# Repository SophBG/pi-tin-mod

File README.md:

# Pi Tin mod

Personal build of jackw01's [Pi Tin](https://github.com/jackw01/pi-tin) (3D-printed clamshell version, KiCad 10). It adds 10 RGB LEDs under the buttons, a centred speaker, a USB-drive mode for the ROMs, and ESD protection on USB, and runs on an Orange Pi Zero 2W. The upstream [build guides](https://jackw01.github.io/pi-tin/) still apply. License: CERN-OHL-W v2.

## Boards

| | Main | Display |
|---|---|---|
| Size | 89.15 × 55.65 mm | 39.15 × 46.15 mm |
| **Thickness** | **1.0 mm** | **0.6 mm** |
| Layers, copper | 2, 1 oz | 2, 1 oz |
| Min. track / hole / via | 0.2 / 0.3 / 0.6 mm | 0.2 / 0.3 / 0.6 mm |

Gerbers for both boards are in `fab/`.

## Main board changes

| Function | Parts | Notes |
|---|---|---|
| RGB LEDs | D1–D10 (WS2812B-2020) | Chain: D1 → D10. D1–D4 ABXY, D5 Start, D6 Select, D7–D10 D-pad. |
| LED driver | U106 74AHCT1G125, R130 330 Ω | Input: SPI MOSI. Enabled only by the second SPI chip select on header pin 21, so the display (first chip select) never reaches the LEDs. |
| | R131 10 k, R132 100 k | R131: buffer off at boot. R132: data line low. |
| USB detect | R133/R134 100 k | VBUS divider to header pin 8 |
| USB-drive mode | U107 USBLC6-2SC6, TP132 (D+), TP133 (D−) | Wire TP132/TP133 by hand to the Orange Pi's USB D+/D− (see Hardware notes). Optional. |
| Backlight PWM | Header pins 16 and 18 swapped | Backlight on pin 16, UP on pin 18 (upstream: the other way round). Pin 16 is a hardware PWM on the Orange Pi. |

**Footprints for both suppliers:**
- **J101:** HCTL HC-TYPE-C-16P-01A or GCT USB4105-GF-A.
- **8-pin FPC:** XYECONN FPC09-Q1.0-8AH2.0 or Molex 200528-0080.
- **50-pin FPC:** JUSHUO AFC07-S50ECA-00 or Amphenol F32Q-1A7H1-11050.

**Not fitted:** C107, C110, C111, D103, FB103, FB104, R103, R109, R118, R125 (main board); J101 (display board).

**LEDs from LCSC:** XINGLIGHT XL-2020RGBC-WS2812B. Check its pin-1 mark before soldering.

## Display

2.8" ILI9341, 240 × 320, 50-pin 0.5 mm FPC, with 4-wire resistive touch. The touch is not used, but it gives the 4.0 mm thickness the case expects and protects the screen.

- **Known good:** Adafruit 1774 (MI0283QT-11), or BuyDisplay ER-TFT028-4 with the "Resistive Touch" option.
- **Outline:** 50.2 × 69.3 × 4.0 mm. Active area: 43.2 × 57.6 mm.
- **FPC:** leaves the middle of a short side, about 25.5 mm wide and 27 mm long. It must have plug-in contacts: 37-pin solder-tail panels don't fit.
- **Pinout:** 1 LEDK · 2–5 LEDA · 6–9 IM0–3 · 10 RESET · 33 SDO · 34 SDI · 35 RD · 36 WRX = D/C · 37 DCX = SCK · 38 CS · 40–42 VCC · 43 GND. Pins 44–47 (touch) only go to test points.
- **Without touch** (2.8 mm thick):
  - **Spacer:** add a 1.2 mm frame between the bezel and the panel, 50.2 × 69.3 mm outside with a 60 × 45.5 mm window (the size of the bezel opening).
  - **Screen protector:** 61–62 × 46–47 mm, for example a protector for the bottom screen of an original 3DS. Subtract its thickness from the frame.

## Speaker

| Space | |
|---|---|
| Outline | 15 × 11 mm |
| Height | 3.4 mm, from the PCB to the faceplate ledge |
| Pads (LS101) | 2.5 × 1.7 mm, centres 9.85 mm apart across the width, about 1 mm from the short end away from the D-pad |

- **Spring contacts (no soldering):** Same Sky CMS-151125-078S-67 (8 Ω) or CMS-151125-076S-67 (6 Ω), 15 × 11 × 2.5 mm. Contacts face the PCB.
- **Wired (soldered):**
  - **Size:** 15 × 11 mm, body at most 3.3 mm tall, 6–8 Ω, 0.5 W or more.
  - **Wiring:** cut the leads to about 1 cm and solder them to the LS101 pads. Polarity does not matter.
  - **Lead routing:** the pocket wall stops 1 mm above the PCB, so the leads pass under it.
- **Taller spring speakers** (for example the 1511 ones with a 3.0–3.3 mm body):
  - **Faceplate:** lower the pocket ledge to the body height plus about 0.4 mm.
  - **Contacts:** the springs must land on the pads.
- **H106 clearance:** the speaker body starts about 0.4 mm past the edge of the H106 mounting hole. Check that the screw head doesn't press on it.

## Other parts

- **Interconnect cable:** 8-pin FFC, 1.0 mm pitch, contacts on the same side.
  - **Length:** **50 mm**. The shortest path through the hinge is about 35–38 mm, and the cable must not be under tension.
  - **Parts:** GCT 10-08-A-0050-C-4-08-4-T or JUSHUO JS10A-08P-050-4-8.
- **Battery:** 1-cell LiPo, about 2000 mAh, 8 × 38 × 60 mm, with protection circuit and a JST PH 2-pin plug, for example PKCell LP803860. The pocket is about 66.8 × 38.8 × 8 mm.
  - **Polarity:** J102 pin 1 is BAT+ (it goes to F101). Check that the red wire lands on it before plugging in.
- **Shoulder buttons:** E-Switch TL3336AF160Q.
- **Wi-Fi antenna:** 2.4/5 GHz flex (FPC) antenna with an **MHF4 (IPEX-4)** plug and 0.81 mm cable, flat part at most about 27 × 12 mm. The one that comes with the board fits the connector; use it if it is small enough. U.FL (MHF1) antennas don't fit this connector.

## 3D printing

- **Faceplate:** `3d/faceplate/faceplate_v3_with_led_pockets.stl`. It is `v3.stl` with the LED pockets and collars merged, plus:
  - **Thicker skin:** most 0.8 mm panels are now 1.7 mm (`faceplate_thickening.stl`). That leaves 1.9 mm above the main board and 2.9 mm above the Orange Pi. The USB-C sits on the back, but its four shell legs come through: trim them flush on the front if they stick out more than 1.5 mm. Left as they were: the button rings, the LED pockets and light tunnels (with 0.5 mm around them), the Start/Select and side buttons, and the speaker.
  - **Over the Orange Pi:** its parts were placed from Orange Pi's DXF of the board; they are in the same places as on the Pi Zero. The panels over the HDMI and the Wi-Fi module stay 0.8 mm. The pocket over the two USB-C leaves 3.4 mm (the connectors are about 3.2 mm).
  - **ABXY LED pockets:** the collars left small gaps beside the cutter (and the one at the bottom right was open on one side); `faceplate_pocket_fill.stl` fills them, so each pocket is exactly the cutter's shape, like the D-pad ones.
  - **Button key tabs:** the light tunnels end where the B (left and right) and Y (bottom) tabs are and had taken their lower 0.8 mm; the tabs are whole again. Light still passes beside and under them.
  - **microSD closure:** 1.7 mm instead of 0.8 mm, leaving 2.9 mm above the Orange Pi for the card and its slot.
  - **To rebuild it:** open `faceplate_led_cuts.scad` with the five STLs in the same folder.
  - **In Blender:** Union with the collars, the pocket fill and the thickening first, then Difference with the cutter, then Union with the key tabs (in the `.scad`), all with the Exact solver.
- **Lower case:** `3d/case/p101_lower_case_fixed.STL`.
- **Display housing, bezel, buttons:** the upstream STL files.

## Orange Pi Zero 2W

`software/orange_pi/` sets everything up on Armbian (Debian, "current" kernel). The sound and backlight drivers are Armbian kernel patches, so mainline kernels won't work. Do the Armbian first-boot setup over SSH, then:

```
cd software/orange_pi
sudo ./install.sh            # ROM_SIZE=16G sudo ./install.sh for a bigger ROM drive
sudo reboot
sudo ./check.sh --test       # status, then backlight, LEDs, sound and buttons
```

What it sets up:
- **Overlay `pitin-opi-zero2w.dts`:**
  - display: `mi0283qt` driver on SPI1 CS0 at 50 MHz, `rotation = <90>` (use 270 if the picture is upside down);
  - backlight: PWM4 at 20 kHz, as `/sys/class/backlight/pitin-backlight`;
  - LEDs: spidev on CS1, with PH8 as the chip select;
  - sound: I2S0 to the MAX98357A, through the Armbian kernel's AHUB driver;
  - the 15 buttons as one gamepad;
  - power button: systemd powers off;
  - power-off line on pin 5;
  - USB cable detect;
  - UART0 off.
- **RetroArch** starts on the screen at boot. There is no EmulationStation.
  - **Save states:** the game state is saved and restored automatically, including at power-off.
  - **Cores:** they come from the Debian packages. If the packaged RetroArch lacks KMS, `install.sh` builds it from source.
- **ROM drive:** a FAT32 image (`~/roms.img`) mounted on `~/roms`, with a folder per console. Plugged into a computer, it shows up there as a USB drive (`pitin-usbd`); a charger changes nothing.
- **Sound:** both channels are mixed for the single amplifier. Set the volume with `amixer sset Master 60%`.
- **`pitin-daemon`:** screen brightness, volume, the LEDs and a settings page (`pitin-web.html`). Settings are kept across reboots.
  - **LED effects:** each LED has its own colour. Off, static (steady), wave (a rainbow, or the LEDs' own colours, travels from LED to LED in a chosen order), fade (all LEDs change colour together) and reactive (a pressed button lights the LEDs beside it: two for the D-pad and ABXY, its own side for the shoulders).
  - **Settings page:** LEDs, uploading ROMs over Wi-Fi (sorted into the console folders by file type) and deleting them, screen brightness, volume, status, the console's name on the network (Console tab, "Change"), restart and power off. Works on a phone or a computer, in French or English depending on the browser's language.
  - **Address:** `http://<name>.local` on most phones and computers (`avahi-daemon`), `http://<name>` on Windows (the daemon answers LLMNR) and on routers that know the names, or `http://<ip>`. Port 80, so no port in the address (8080 if 80 is taken; `WEB_PORT=` in `/etc/default/pitin`). The page shows the addresses that work from the device it is open on.
  - **Console's OK:** off at first: anyone on the same Wi-Fi can open the page. Switch it on in the Console tab ("New devices need the console's OK"): when a new phone or computer opens the page, the console pauses the game and shows a card asking whether to let it in, with the kind of device (iPhone, Windows PC…) under it. Hold A for a second: yes; B: no; after a minute it gives up. One device at a time, so the answer goes to the one named on the screen. A device let in stays in until it signs out or the switch is turned off. Locked out: `sudo rm /var/lib/pitin/sessions.json` over SSH.
  - **On-screen messages:** the daemon's hotkeys (screen brightness, volume, LEDs) show their value as RetroArch on-screen text; RetroArch's own hotkeys show RetroArch's messages. Volume is the same "Master" volume as on the settings page.
  - **LED auto brightness:** on by default (switch on the settings page). The LEDs dim with the screen, so the screen brightness hotkey sets both; the LED brightness setting is then their maximum, at full screen brightness, and the page shows the brightness they have now.
  - **Load, restart and quit:** SPECIAL + L1, + B and + START act only when held for a second, so a slip doesn't lose progress. Quitting saves the game state (`savestate_auto_save`), and it is loaded again when the game starts.
  - **List of hotkeys:** SPECIAL + SELECT pauses the game and shows every SPECIAL hotkey on a card (a RetroArch overlay, `overlay/`). While it is open, the buttons do the same without SPECIAL (volume, brightness, LEDs, save, slot…); SELECT closes it.
  - **Changing the cards:** edit the texts or colours in `overlay/make_card.py` and run it, or edit the PNGs (320 × 240, transparent around the card) in any image editor; then run `install.sh` again.
  - **How:** the messages, quit / reset and the card use RetroArch's network commands (UDP 55355, also reachable from the local network). Language: `LANGUAGE=` in `/etc/default/pitin` (`en` or `fr`; empty = the system's language), then run `install.sh` again for the card.

Hotkeys (hold SPECIAL):

| SPECIAL + | Action |
|---|---|
| X | RetroArch menu |
| L1 (hold 1 s) / R1 | Load / save state |
| LEFT / RIGHT | Previous / next save slot |
| UP / DOWN | Volume up / down |
| B (hold 1 s) | Reset |
| START (hold 1 s) | Quit the game (it is saved) |
| L2 / R2 | Screen brightness down / up |
| Y | LEDs on / off (they come back with the same effect) |
| A | Next LED effect |
| SELECT | List of hotkeys on the screen |

Pins that change role:

| Pin | Pi Tin use | On the Orange Pi |
|---|---|---|
| 5 | `SHUTDOWN_PS`: power-off output | PI7: gpio-poweroff, active low |
| 8 / 10 | `USB_PWR` (USB detect) / RIGHT | PH0 / PH1: the UART0 debug console, disabled by the overlay. U-Boot still uses it, so don't hold RIGHT while booting. |
| 12 / 35 / 40 | I2S BCLK / LRCLK / DATA | PI1 / PI2 / PI3 (I2S0) |
| 16 | Backlight PWM (`RS/BL` on the display board) | PI14: PWM4 |
| 18 | UP | PH4: plain input |
| 21 | `LED_CS`: gates the LED buffer | PH8 as a GPIO chip select (`cs-gpios`) |
| 26 | `SHUTDOWN_PI`: power button | PH9, which is also SPI1 CS1: used as a plain input |

**Not tested on hardware.** Sound is the least certain part: it relies on the AHUB driver and on overlay settings reported working on this board on the DietPi forum. `check.sh` shows which part failed. `install.sh` stops if the overlay doesn't apply to the board's device tree.

Hardware notes:
- **USB-drive mode:** TP132/TP133 must go to the D+/D− of the OTG USB-C port (USB0). The D+/D− pads under the board look like they belong to the host-only port; check with a multimeter.
- **Top side:** the main PCB covers a strip of about 6 mm along the header, so nothing there may stick up.
- **Bottom side:** it faces the battery and has an SPI flash chip about 1.5 mm tall. Use thicker foam or Kapton there.
- **Wi-Fi antenna:** the Orange Pi Zero 2W has no antenna on the board, only an IPEX-4 (MHF4) connector next to the 24-pin FPC (ANT1 in the schematic), and without one there is no Wi-Fi. The faceplate has a pocket over that connector and a channel into the thin panel over the Wi-Fi module, for the plug and its cable. Stick a small flex antenna to the inside of that panel (room: about 27 × 12 mm) and coil the spare cable there. The boards are close, so the range is shorter than with the antenna outside the case: check it before closing the case.

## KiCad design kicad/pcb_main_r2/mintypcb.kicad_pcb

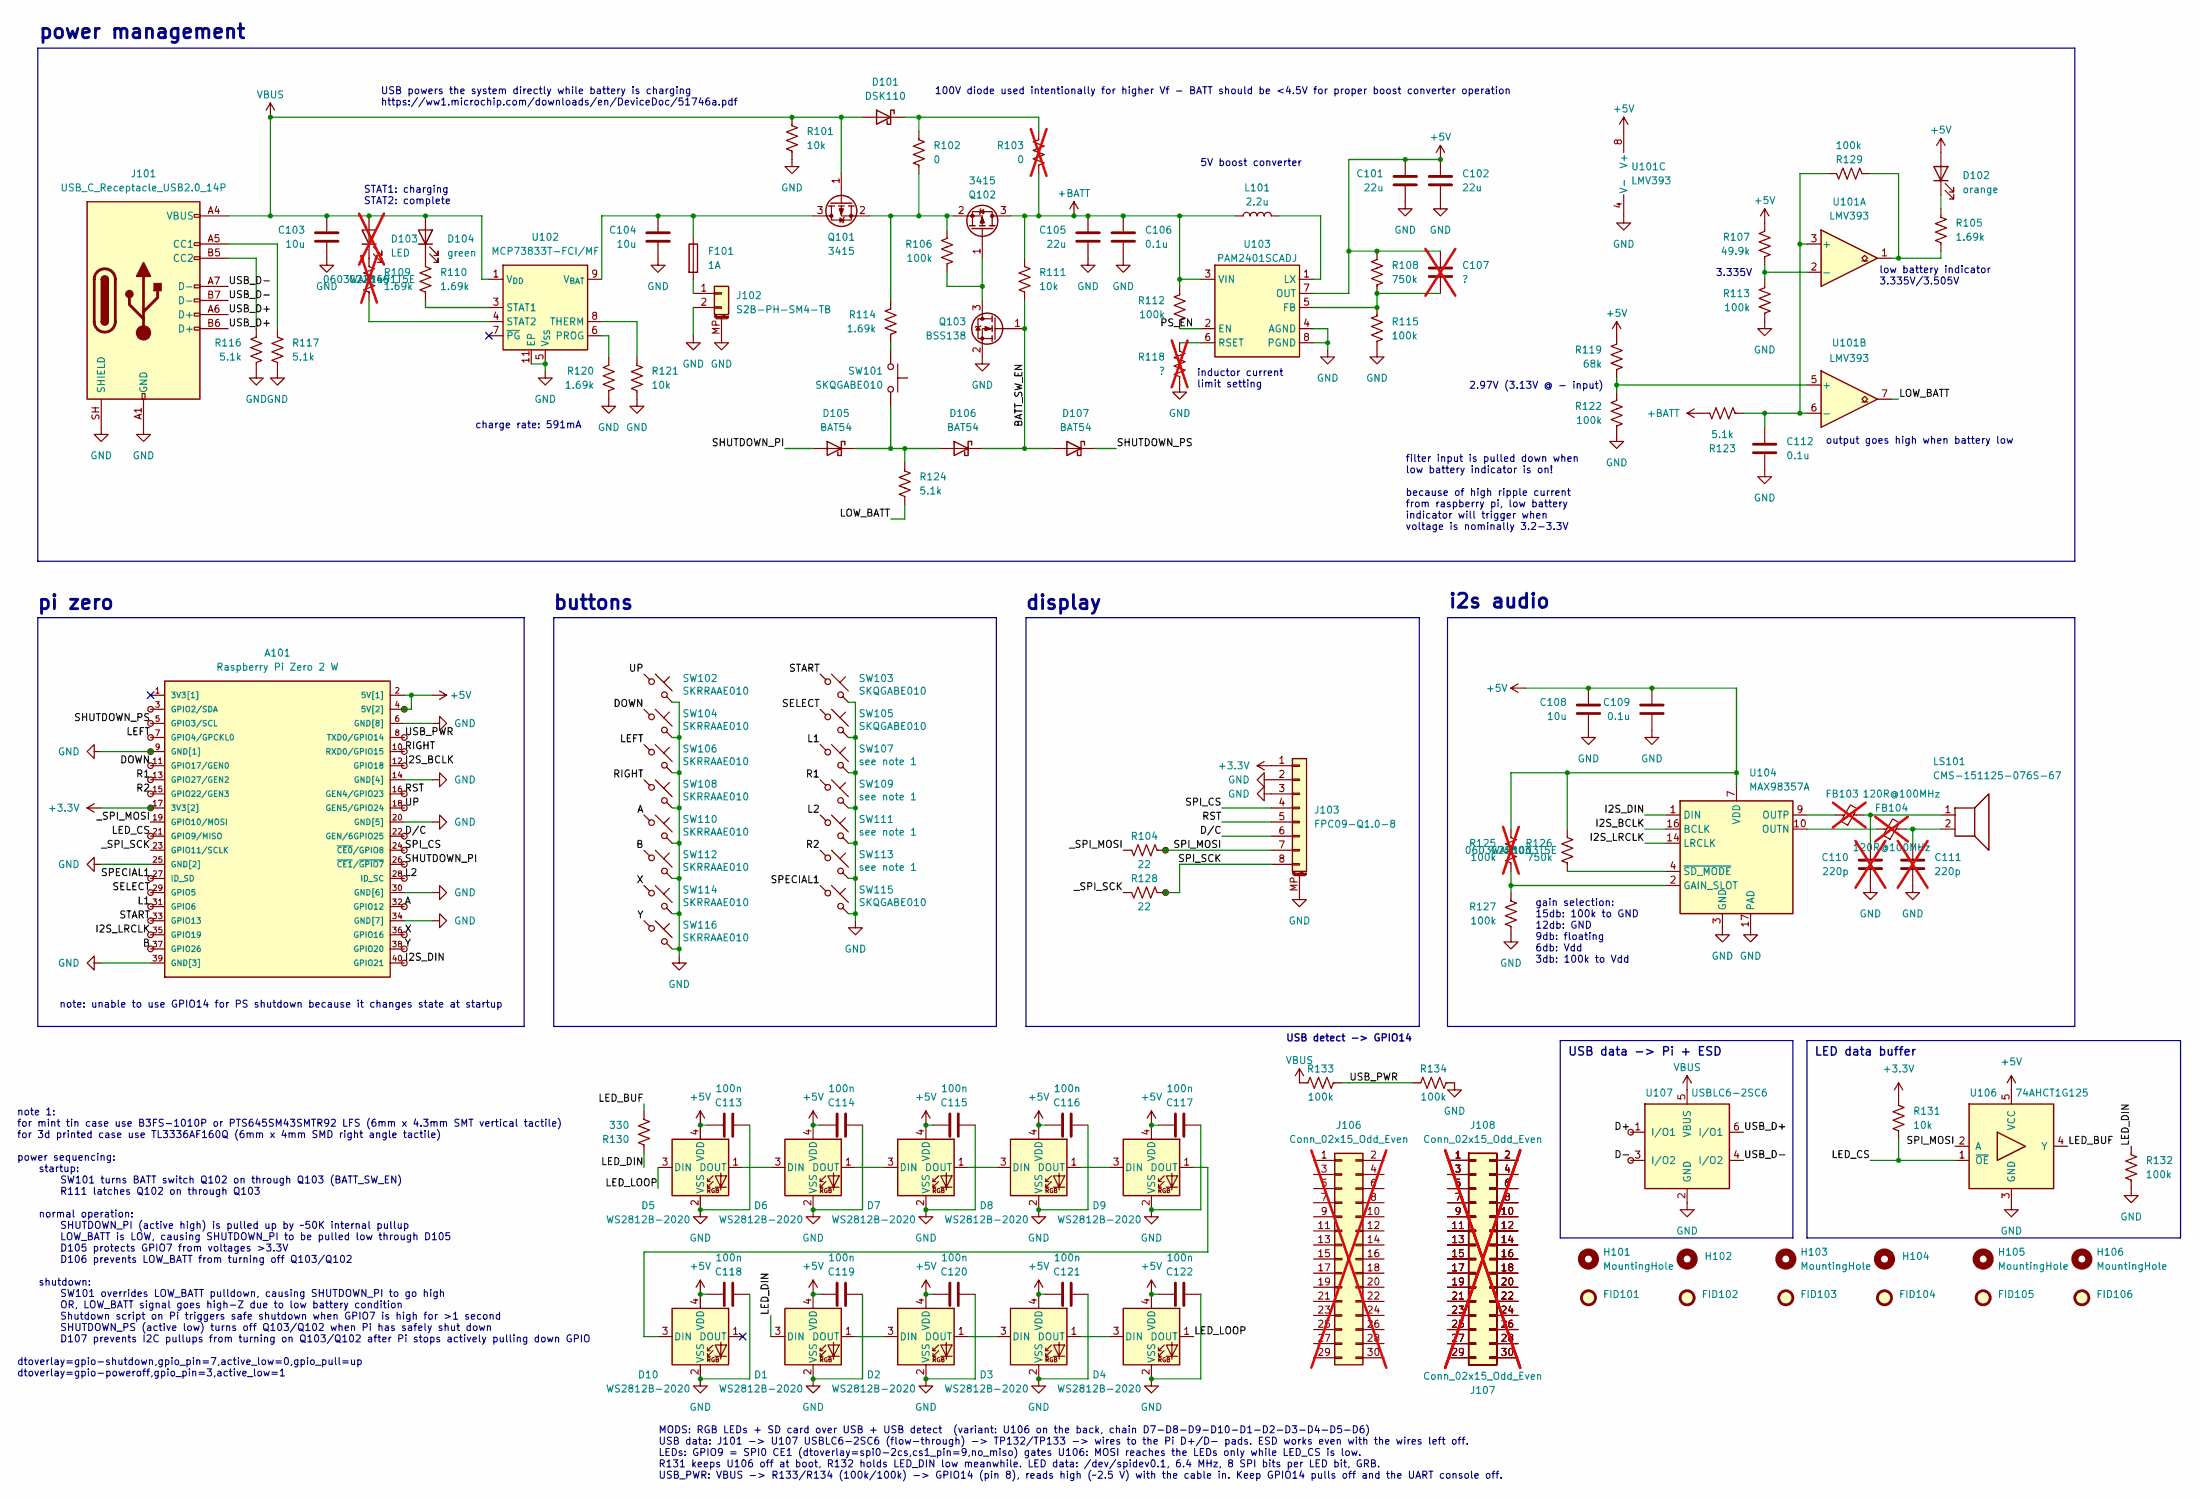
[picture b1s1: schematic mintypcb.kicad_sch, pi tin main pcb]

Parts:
A101: Raspberry Pi Zero 2 W; RASPBERRYPI-ZERO_RPI-ZERO_pi_tin; MPN (Alternate) SC1176
C101, C102, C105: 22u; C_1206_3216Metric; MPN CL31B226KPHNNNE; LCSC C87996
C103, C104, C108: 10u; C_0805_2012Metric; MPN CL21B106KPQNNNE; LCSC C32635
C106, C109, C112: 0.1u; C_0603_1608Metric; MPN CC0603KRX7R9BB104; LCSC C14663
C107: ?; C_0603_1608Metric; not fitted
C110, C111: 220p; C_0603_1608Metric; MPN (Alternate) CL10C221JB8NNNC; not fitted
C113, C114, C115, C116, C117, C118, C119, C120, C121, C122: 100n; C_0603_1608Metric; MPN CC0603KRX7R9BB104; LCSC C14663
D1, D2, D3, D4, D5, D6, D7, D8, D9, D10: WS2812B-2020; LED_WS2812B-2020_PLCC4_2.0x2.0mm
D101: DSK110; D_SOD-123F; MPN DSK110 K110; LCSC C64888
D102: orange; LED_0603_1608Metric; MPN LTST-C190KFKT; LCSC C157740
D103: LED; LED_0603_1608Metric; not fitted
D104: green; LED_0603_1608Metric; MPN LTST-C190TGKT; LCSC C364559
D105, D106, D107: BAT54; D_SOD-323; MPN BAT54WS-7-F; LCSC C124205
F101: 1A; Fuse_0603_1608Metric; MPN 0467001.NRHF; LCSC C151139
FB103, FB104: 120R@100MHz; R_0603_1608Metric_Bridged; MPN (Alternate) BLM18AG121SZ1D; not fitted
FID101, FID102, FID103, FID104, FID105, FID106: Fiducial_1mm_Mask2mm
H101, H103, H105, H106: MountingHole; MountingHole_2.2mm_M2_Mask_tight
H102, H104: ToolingHole; JLC_tooling_hole
J101: USB_C_Receptacle_USB2.0_14P; USB_C_Receptacle_HCTL_HC-TYPE-C-16P-01A_or_GCT_USB4105-GF-A
J102: S2B-PH-SM4-TB; JST_PH_S2B-PH-SM4-TB_1x02-1MP_P2.00mm_Horizontal; MPN S2B-PH-SM4-TB; LCSC C295747
J103: FPC09-Q1.0-8; FPC_1x08_P1.00mm_XYECONN_FPC09-Q1.0-8AH2.0_or_Molex_200528-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; MPN FPC09-Q1.0-8AH2.0; LCSC C19269923
J106: Conn_02x15_Odd_Even; pi_tin_pi_simulator; not fitted
J107: Conn_02x15_Odd_Even; pi_tin_pi_simulator_lands; not fitted
J108: Conn_02x15_Odd_Even; pi_tin_pi_simulator_tp; not fitted
L101: 2.2u; L_3225DFN; MPN FTC322512S2R2MBCA; LCSC C5832385
LS101: CMS-151125-076S-67; Speaker_CUI_CMR-1206S-67; MPN (Alternate) CMS-151125-076S-67
Q101, Q102: 3415; SOT-23; MPN 3415A; LCSC C337518
Q103: BSS138; SOT-323_SC-70; MPN BSS138W-7-F; LCSC C24553
R101, R111, R121, R131: 10k; R_0603_1608Metric; MPN 0603WAF1002T5E; LCSC C25804
R102: 0; R_0603_1608Metric_Bridged
R103: 0; R_0603_1608Metric; not fitted
R104, R128: 22; R_0603_1608Metric; MPN 0603WAF220JT5E; LCSC C23345
R105, R110, R114, R120: 1.69k; R_0603_1608Metric; MPN 0603WAF1691T5E; LCSC C22846
R106, R112, R113, R115, R122, R127, R129, R132, R133, R134: 100k; R_0603_1608Metric; MPN 0603WAF1003T5E; LCSC C25803
R107: 49.9k; R_0603_1608Metric; MPN 0603WAF4992T5E; LCSC C23184
R108, R126: 750k; R_0603_1608Metric; MPN 0603WAF7503T5E; LCSC C23240
R109: 1.69k; R_0603_1608Metric; MPN 0603WAF1691T5E; LCSC C22846; not fitted
R116, R117, R123, R124: 5.1k; R_0603_1608Metric; MPN 0603WAF5101T5E; LCSC C23186
R118: ?; R_0603_1608Metric; not fitted
R119: 68k; R_0603_1608Metric; MPN 0603WAF6802T5E; LCSC C23231
R125: 100k; R_0603_1608Metric; MPN 0603WAF1003T5E; LCSC C25803; not fitted
R130: 330; R_0603_1608Metric; MPN 0603WAF3300T5E; LCSC C23138
SW101, SW103, SW105, SW115: SKQGABE010; SW_PTS526; MPN SKQGABE010; LCSC C115351
SW102, SW104, SW106, SW108, SW110, SW112, SW114, SW116: SKRRAAE010; SW_SKRR; MPN SKRRAAE010; LCSC C97437
SW107, SW109, SW111, SW113: see note 1; SW_TL3336AF160Q_or_PTS645_paste1; MPN (Alternate) TL3336AF160Q; LCSC C231324
TP101, TP102, TP103, TP104, TP105, TP106, TP107, TP108, TP109, TP110, TP111, TP112, TP113, TP114, TP115, TP116, TP117, TP118, TP119, TP120, TP121, TP122, TP123, TP124, TP125, TP126, TP127, TP128, TP129, TP130, TP131: TestPoint_Small; TestPoint_Pad_D1.5mm
TP132: USB_D+; TestPoint_Pad_D1.5mm
TP133: USB_D-; TestPoint_Pad_D1.5mm
U101: LMV393; MSOP-8_3x3mm_P0.65mm; MPN LMV393M8-13; LCSC C460091
U102: MCP73833T-FCI/MF; DFN-10-1EP_3x3mm_P0.5mm_EP1.58x2.35mm; MPN MCP73833T-FCI/MF; LCSC C511337
U103: PAM2401SCADJ; MSOP-8_3x3mm_P0.65mm; MPN PAM2401SCADJ; LCSC C508238
U104: MAX98357A; TQFN-16-1EP_3x3mm_P0.5mm_EP1.23x1.23mm; MPN MAX98357AETE+T; LCSC C910544
U106: 74AHCT1G125; SOT-23-5; MPN SN74AHCT1G125DBVR; LCSC C7484
U107: USBLC6-2SC6; SOT-23-6; MPN USBLC6-2SC6; LCSC C7519

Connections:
+3.3V: A101.17 (3V3[2]), J103.1, R131.2, TP113.1 (1_1)
+5V: A101.2 (5V[1]), A101.4 (5V[2]), C101.1, C102.1, C107.1, C108.1, C109.1, C113.1, C114.1, C115.1, C116.1, C117.1, C118.1, C119.1, C120.1, C121.1, C122.1, D1.4 (VDD), D2.4 (VDD), D3.4 (VDD), D4.4 (VDD), D5.4 (VDD), D6.4 (VDD), D7.4 (VDD), D8.4 (VDD), D9.4 (VDD), D10.4 (VDD), D102.2 (A), R107.2, R108.1, R119.2, R125.1, R126.1, TP102.1 (1_1), U101.8 (V+), U103.7 (OUT), U104.7 (VDD), U104.8 (VDD), U106.5 (VCC)
+BATT: C105.1, C106.1, L101.1, Q102.3 (D), R103.1, R111.2, R112.2, R123.1, U103.3 (VIN)
/A: A101.32 (GPIO12), SW110.1, TP125.1 (1_1)
/B: A101.37 (GPIO26), SW112.1, TP129.1 (1_1)
/BATT_SW_EN: D106.1 (K), D107.2 (A), Q103.1 (G), R111.1
/D+: TP132.1, U107.1 (I/O1)
/D-: TP133.1, U107.3 (I/O2)
/DOWN: A101.11 (GPIO17/GEN0), SW104.1, TP108.1 (1_1)
/D/C: A101.22 (GEN/6GPIO25), J103.6, TP117.1 (1_1)
/I2S_BCLK: A101.12 (GPIO18), TP109.1 (1_1), U104.16 (BCLK)
/I2S_DIN: A101.40 (GPIO21), TP131.1 (1_1), U104.1 (DIN)
/I2S_LRCLK: A101.35 (GPIO19), TP127.1 (1_1), U104.14 (LRCLK)
/L1: A101.31 (GPIO6), SW107.1, TP124.1 (1_1)
/L2: A101.28 (ID_SC), SW111.1, TP122.1 (1_1)
/LED_BUF: R130.1, U106.4 (Y)
/LED_CS: A101.21 (GPIO9/MISO), R131.1, TP116.1 (1_1), U106.1 (~OE)
/LED_DIN: D1.3 (DIN), R130.2, R132.1
/LED_LOOP: D4.1 (DOUT), D5.3 (DIN)
/LEFT: A101.7 (GPIO4/GPCKL0), SW106.1, TP104.1 (1_1)
/LOW_BATT: R124.1, U101.7
/PS_EN: R112.1, U103.2 (EN)
/R1: A101.13 (GPIO27/GEN2), SW109.1, TP110.1 (1_1)
/R2: A101.15 (GPIO22/GEN3), SW113.1, TP111.1 (1_1)
/RIGHT: A101.10 (RXD0/GPIO15), SW108.1, TP107.1 (1_1)
/SELECT: A101.29 (GPIO5), SW105.1, TP123.1 (1_1)
/SHUTDOWN_PI: A101.26 (~CE1/~GPIO7), D105.2 (A), TP120.1 (1_1)
/SHUTDOWN_PS: A101.5 (GPIO3/SCL), D107.1 (K), TP103.1 (1_1)
/SPECIAL1: A101.27 (ID_SD), SW115.1, TP121.1 (1_1)
/SPI_CS: A101.24 (~CE0/GPIO8), J103.4, TP119.1 (1_1)
/SPI_MOSI: J103.7, R104.1, TP115.1 (1_1), U106.2 (A)
/SPI_SCK: J103.8, R128.1, TP118.1 (1_1)
/START: A101.33 (GPIO13), SW103.1, TP126.1 (1_1)
/USB_D+: J101.A6 (D+), J101.B6 (D+), U107.6 (I/O1)
/USB_D-: J101.A7 (D-), J101.B7 (D-), U107.4 (I/O2)
/USB_PWR: A101.8 (TXD0/GPIO14), R133.2, R134.1, TP105.1 (1_1)
/X: A101.36 (GPIO16), SW114.1, TP128.1 (1_1)
/Y: A101.38 (GPIO20), SW116.1, TP130.1 (1_1)
/_SPI_MOSI: A101.19 (GPIO10/MOSI), R104.2
/_SPI_SCK: A101.23 (GPIO11/SCLK), R128.2
GND: A101.6 (GND[8]), A101.9 (GND[1]), A101.14 (GND[4]), A101.20 (GND[5]), A101.25 (GND[2]), A101.30 (GND[6]), A101.34 (GND[7]), A101.39 (GND[3]), C101.2, C102.2, C103.2, C104.2, C105.2, C106.2, C108.2, C109.2, C110.2, C111.2, C112.2, C113.2, C114.2, C115.2, C116.2, C117.2, C118.2, C119.2, C120.2, C121.2, C122.2, D1.2 (VSS), D2.2 (VSS), D3.2 (VSS), D4.2 (VSS), D5.2 (VSS), D6.2 (VSS), D7.2 (VSS), D8.2 (VSS), D9.2 (VSS), D10.2 (VSS), J101.A1 (GND), J101.A12 (GND), J101.B1 (GND), J101.B12 (GND), J101.SH (SHIELD), J102.2, J102.MP (MountPin), J103.2, J103.3, J103.MP (MountPin), Q103.2 (S), R101.1, R113.1, R115.2, R116.1, R117.1, R118.2, R120.1, R121.1, R122.1, R127.2, R132.2, R134.2, SW102.2, SW103.2, SW104.2, SW105.2, SW106.2, SW107.2, SW108.2, SW109.2, SW110.2, SW111.2, SW112.2, SW113.2, SW114.2, SW115.2, SW116.2, TP106.1 (1_1), U101.4 (V-), U102.5 (V_{SS}), U102.11 (EP), U103.4 (AGND), U103.8 (PGND), U104.3 (GND), U104.11 (GND), U104.15 (GND), U104.17 (PAD), U106.3 (GND), U107.2 (GND)
unnamed: A101.3 (GPIO2/SDA), TP101.1 (1_1)
unnamed: C110.1, FB103.2, LS101.1
unnamed: C111.1, FB104.2, LS101.2
unnamed: D1.1 (DOUT), D2.3 (DIN)
unnamed: D2.1 (DOUT), D3.3 (DIN)
unnamed: D3.1 (DOUT), D4.3 (DIN)
unnamed: D5.1 (DOUT), D6.3 (DIN)
unnamed: D6.1 (DOUT), D7.3 (DIN)
unnamed: D7.1 (DOUT), D8.3 (DIN)
unnamed: D8.1 (DOUT), D9.3 (DIN)
unnamed: D9.1 (DOUT), D10.3 (DIN)
unnamed: D101.1 (K), R102.2, R103.2
unnamed: D102.1 (K), R105.2
unnamed: D103.1 (K), R109.2
unnamed: D104.1 (K), R110.2
unnamed: D105.1 (K), D106.2 (A), R124.2, SW101.1
unnamed: J101.A5 (CC1), R117.2
unnamed: J101.B5 (CC2), R116.2
unnamed: F101.2, J102.1
unnamed: J107.1, J108.1
unnamed: J107.2, J108.2
unnamed: J107.3, J108.3
unnamed: J107.4, J108.4
unnamed: J107.5, J108.5
unnamed: J107.6, J108.6
unnamed: J107.7, J108.7
unnamed: J107.8, J108.8
unnamed: J107.9, J108.9
unnamed: J107.10, J108.10
unnamed: J107.11, J108.11
unnamed: J107.12, J108.12
unnamed: J107.13, J108.13
unnamed: J107.14, J108.14
unnamed: J107.15, J108.15
unnamed: J107.16, J108.16
unnamed: J107.17, J108.17
unnamed: J107.18, J108.18
unnamed: J107.19, J108.19
unnamed: J107.20, J108.20
unnamed: J107.21, J108.21
unnamed: J107.22, J108.22
unnamed: J107.23, J108.23
unnamed: J107.24, J108.24
unnamed: J107.25, J108.25
unnamed: J107.26, J108.26
unnamed: J107.27, J108.27
unnamed: J107.28, J108.28
unnamed: J107.29, J108.29
unnamed: J107.30, J108.30
unnamed: C104.1, F101.1, Q101.3 (D), U102.9 (V_{BAT}), U102.10 (V_{BAT})
unnamed: Q101.2 (S), Q102.2 (S), R102.1, R106.2, R114.2
unnamed: Q102.1 (G), Q103.3 (D), R106.1
unnamed: R105.1, R129.2, U101.1
unnamed: R114.1, SW101.2
unnamed: C112.1, R123.2, R129.1, U101.3 (+), U101.6 (-)
unnamed: R107.1, R113.2, U101.2 (-)
unnamed: R119.1, R122.2, U101.5 (+)
unnamed: R120.2, U102.6 (PROG)
unnamed: R110.1, U102.3 (STAT1)
unnamed: R109.1, U102.4 (STAT2)
unnamed: R121.2, U102.8 (THERM)
unnamed: C107.2, R108.2, R115.1, U103.5 (FB)
unnamed: L101.2, U103.1 (LX)
unnamed: R118.1, U103.6 (RSET)
unnamed: R125.2, R127.1, U104.2 (GAIN_SLOT)
unnamed: FB104.1, U104.10 (OUTN)
unnamed: FB103.1, U104.9 (OUTP)
unnamed: R126.2, U104.4 (~SD_MODE)
VBUS: C103.1, D101.2 (A), D103.2 (A), D104.2 (A), J101.A4 (VBUS), J101.A9 (VBUS), J101.B4 (VBUS), J101.B9 (VBUS), Q101.1 (G), R101.2, R133.1, U102.1 (V_{DD}), U102.2 (V_{DD}), U107.5 (VBUS)

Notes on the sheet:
i2s audio
low battery indicator 3.335V/3.505V
2.97V (3.13V @ - input)
USB powers the system directly while battery is charging https://ww1.microchip.com/downloads/en/DeviceDoc/51746a.pdf
note: unable to use GPIO14 for PS shutdown because it changes state at startup
5V boost converter
display
pi zero
note 1: for mint tin case use B3FS-1010P or PTS645SM43SMTR92 LFS (6mm x 4.3mm SMT vertical tactile) for 3d printed case use TL3336AF160Q (6mm x 4mm SMD right angle tactile) power sequencing: startup: SW101 turns BATT switch Q102 on through Q103 (BATT_SW_EN) R111 latches Q102 on through Q103 normal 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
3.335V
power management
filter input is pulled down when low battery indicator is on! because of high ripple current from raspberry pi, low battery indicator will trigger when voltage is nominally 3.2-3.3V
output goes high when battery low
charge rate: 591mA
buttons
STAT1: charging STAT2: complete
inductor current limit setting
100V diode used intentionally for higher Vf - BATT should be <4.5V for proper boost converter operation
gain selection: 15db: 100k to GND 12db: GND 9db: floating 6db: Vdd 3db: 100k to Vdd
USB data -> Pi + ESD
LED data buffer
USB detect -> GPIO14
MODS: RGB LEDs + SD card over USB + USB detect (variant: U106 on the back, chain D7-D8-D9-D10-D1-D2-D3-D4-D5-D6) USB data: J101 -> U107 USBLC6-2SC6 (flow-through) -> TP132/TP133 -> wires to the Pi D+/D- pads. ESD works even with the wires left off. LEDs: GPIO9 = SPI0 CE1 (dtoverlay=spi0-2cs,cs1_pin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

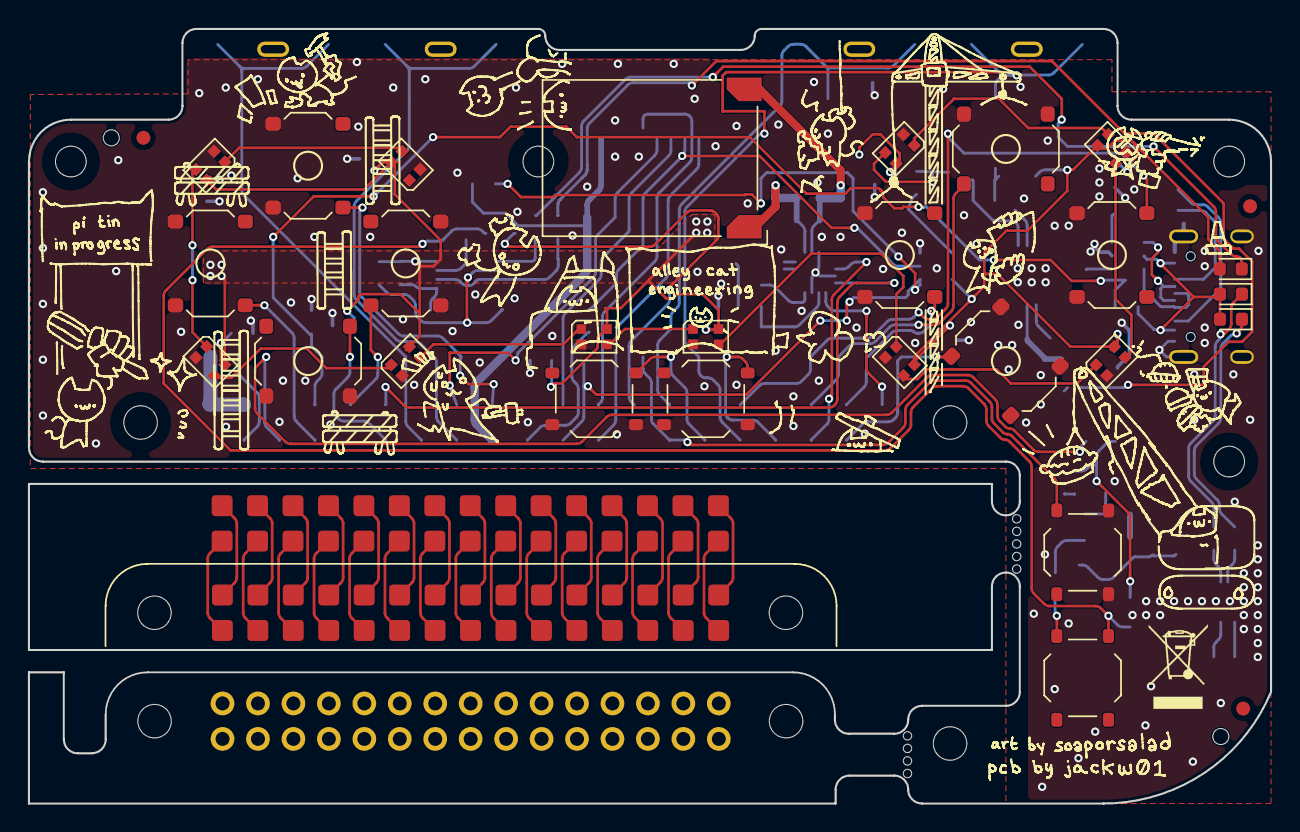
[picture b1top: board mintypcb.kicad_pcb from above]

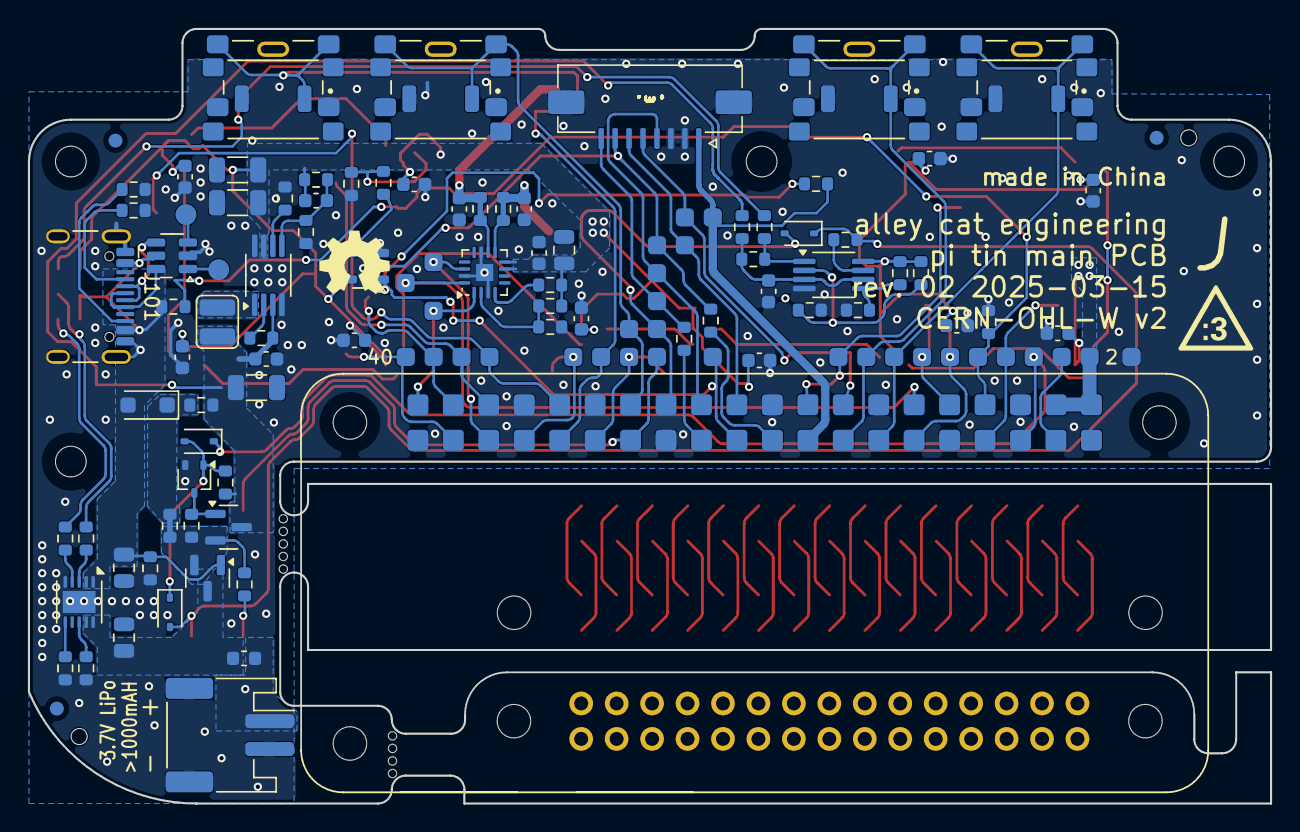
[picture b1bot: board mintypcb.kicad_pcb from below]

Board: 2 copper layers, 89.0 x 55.5 mm, 155 parts (118 on the bottom side), 112 nets.

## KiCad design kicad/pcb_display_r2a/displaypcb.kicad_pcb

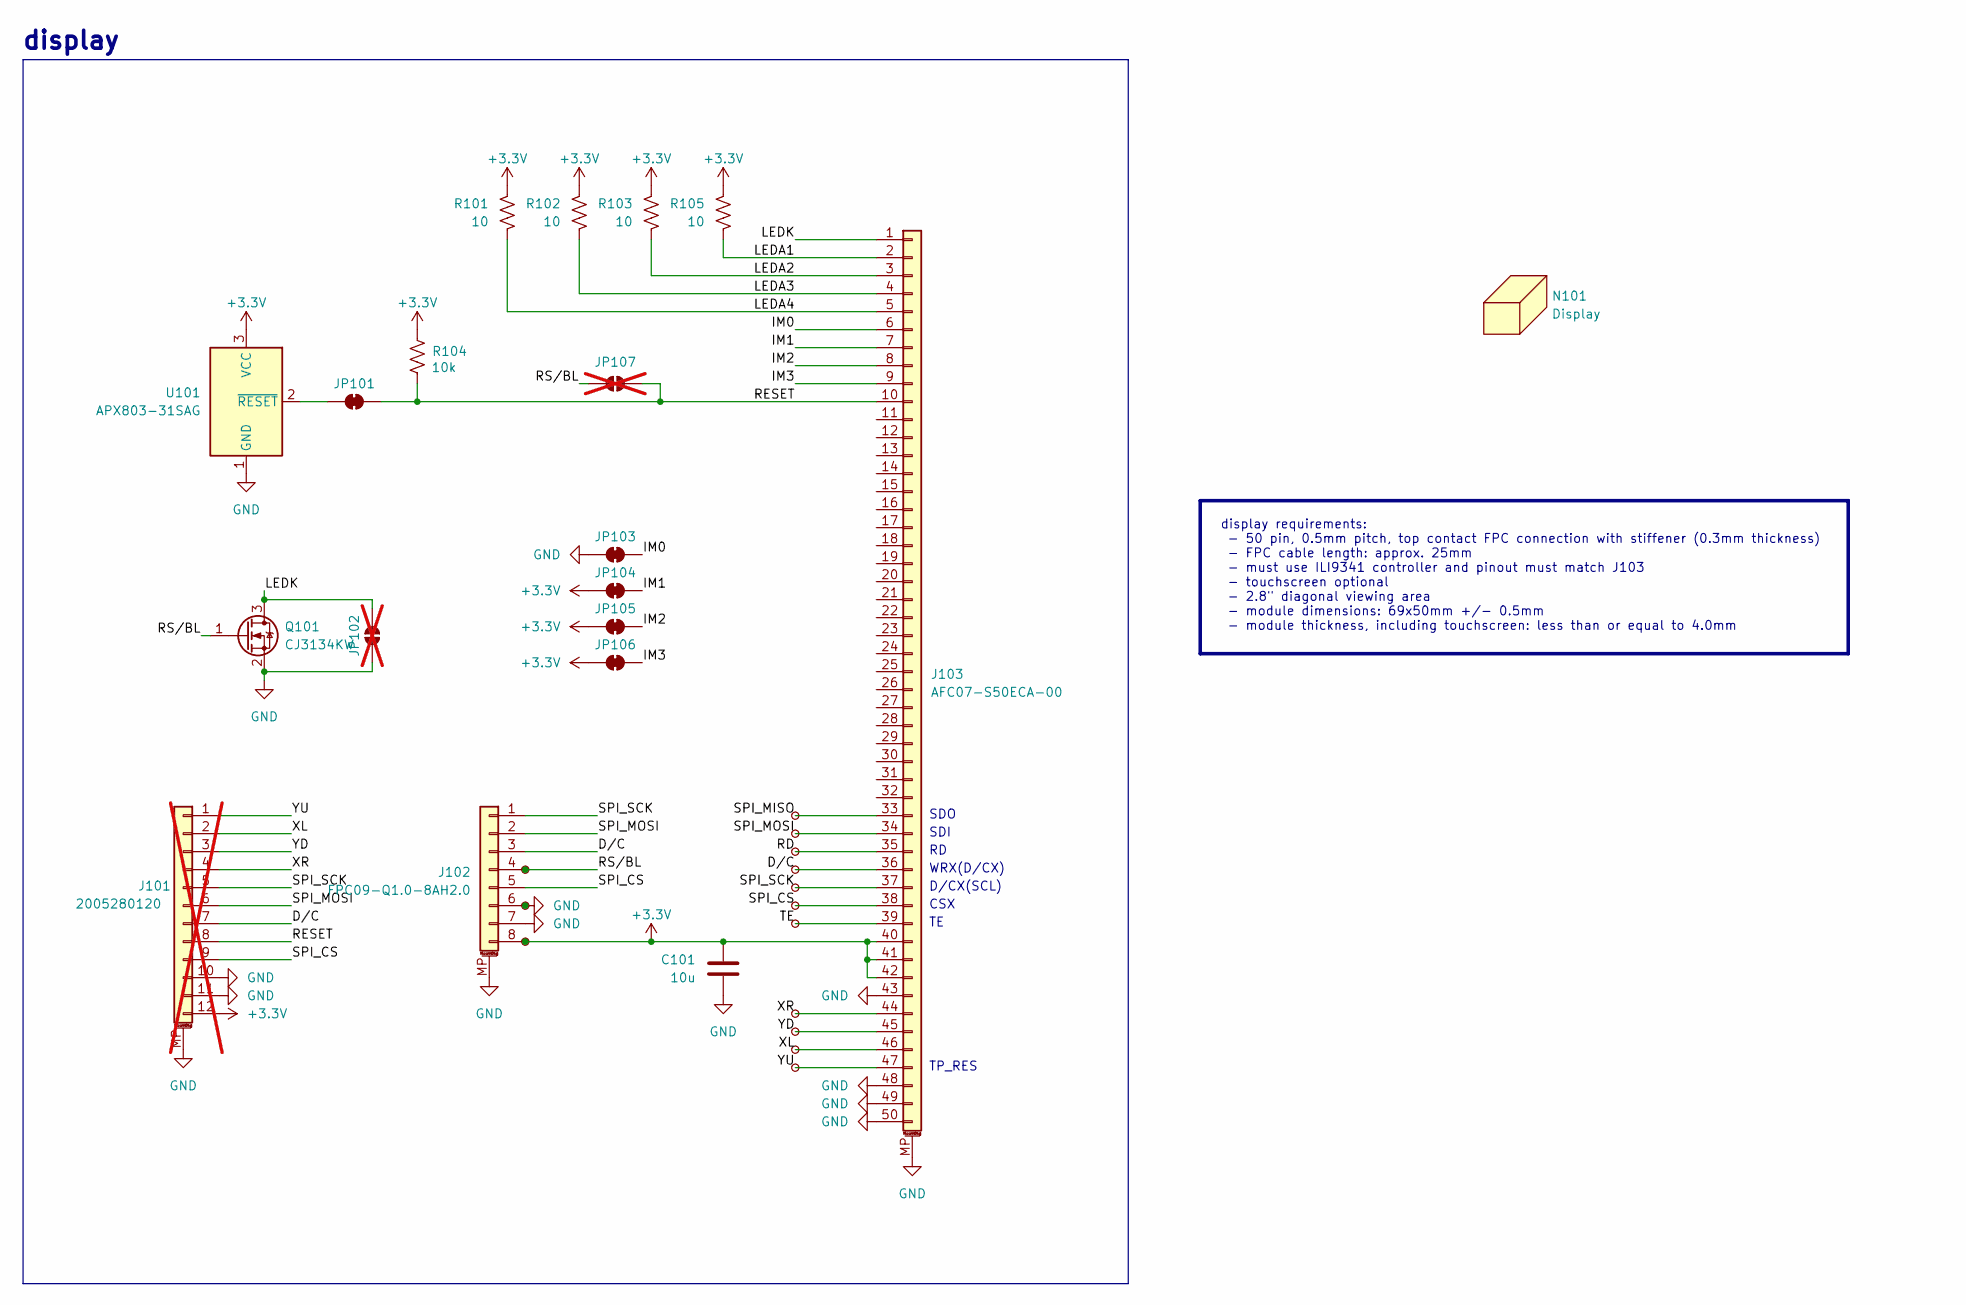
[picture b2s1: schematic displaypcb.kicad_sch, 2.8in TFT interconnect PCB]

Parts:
C101: 10u; C_0805_2012Metric; MPN CL21B106KPQNNNE; LCSC C32635
J101: 2005280120; Molex_200528-0120_1x12-1MP_P1.00mm_Horizontal; MPN 2005280120; not fitted
J102: FPC09-Q1.0-8AH2.0; FPC_1x08_P1.00mm_XYECONN_FPC09-Q1.0-8AH2.0_or_Molex_200528-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; MPN FPC09-Q1.0-8AH2.0; LCSC C19269923
J103: AFC07-S50ECA-00; Jushuo_AFC07-S50ECA-00; MPN AFC07-S50ECA-00; LCSC C262650
JP101, JP103, JP104, JP105, JP106: SolderJumper_2_Bridged; R_0402_1005Metric_bridged
JP102, JP107: SolderJumper_2_Open; R_0402_1005Metric; not fitted
N101: Display; TFT_2.8in_ILI9341
Q101: CJ3134KW; SOT-323_SC-70; MPN CJ3134KW; LCSC C110101
R101, R102, R103, R105: 10; R_0603_1608Metric; MPN 0603WAF100JT5E; LCSC C22859
R104: 10k; R_0603_1608Metric; MPN 0603WAF1002T5E; LCSC C25804
TP101, TP102, TP103, TP104, TP105, TP106, TP107, TP108, TP109, TP110, TP111, TP112, TP113, TP114: TestPoint_Small; TestPoint_Pad_D1.5mm
U101: APX803-31SAG; SOT-23; MPN APX803-31SAG-7; LCSC C460552

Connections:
+3.3V: C101.1, J101.12, J102.8, J103.40, J103.41, J103.42, JP104.1 (A), JP105.1 (A), JP106.1 (A), R101.2, R102.2, R103.2, R104.1, R105.2, TP102.1, U101.3 (VCC)
/D/C: J101.7, J102.3, J103.36, TP107.1
/IM0: J103.6, JP103.2 (B)
/IM1: J103.7, JP104.2 (B)
/IM2: J103.8, JP105.2 (B)
/IM3: J103.9, JP106.2 (B)
/LEDA1: J103.2, R105.1
/LEDA2: J103.3, R103.1
/LEDA3: J103.4, R102.1
/LEDA4: J103.5, R101.1
/LEDK: J103.1, JP102.2 (B), Q101.3 (D)
/RD: J103.35, TP106.1
/RESET: J101.8, J103.10, JP101.2 (B), JP107.2 (B), R104.2
/RS/BL: J102.4, JP107.1 (A), Q101.1 (G), TP103.1
/SPI_CS: J101.9, J102.5, J103.38, TP109.1
/SPI_MISO: J103.33, TP104.1
/SPI_MOSI: J101.6, J102.2, J103.34, TP105.1
/SPI_SCK: J101.5, J102.1, J103.37, TP108.1
/TE: J103.39, TP110.1
/XL: J101.2, J103.46, TP113.1
/XR: J101.4, J103.44, TP111.1
/YD: J101.3, J103.45, TP112.1
/YU: J101.1, J103.47, TP114.1
GND: C101.2, J101.10, J101.11, J101.MP (MountPin), J102.6, J102.7, J102.MP (MountPin), J103.43, J103.48, J103.49, J103.50, J103.MP (MountPin), JP102.1 (A), JP103.1 (A), Q101.2 (S), TP101.1, U101.1 (GND)
unnamed: JP101.1 (A), U101.2 (~RESET)

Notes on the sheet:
display
CSX
WRX(D/CX)
D/CX(SCL)
SDI
TP_RES
SDO
display requirements: - 50 pin, 0.5mm pitch, top contact FPC connection with stiffener (0.3mm thickness) - FPC cable length: approx. 25mm - must use ILI9341 controller and pinout must match J103 - touchscreen optional - 2.8" diagonal viewing area - module dimensions: 69x50mm +/- 0.5mm - module thic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

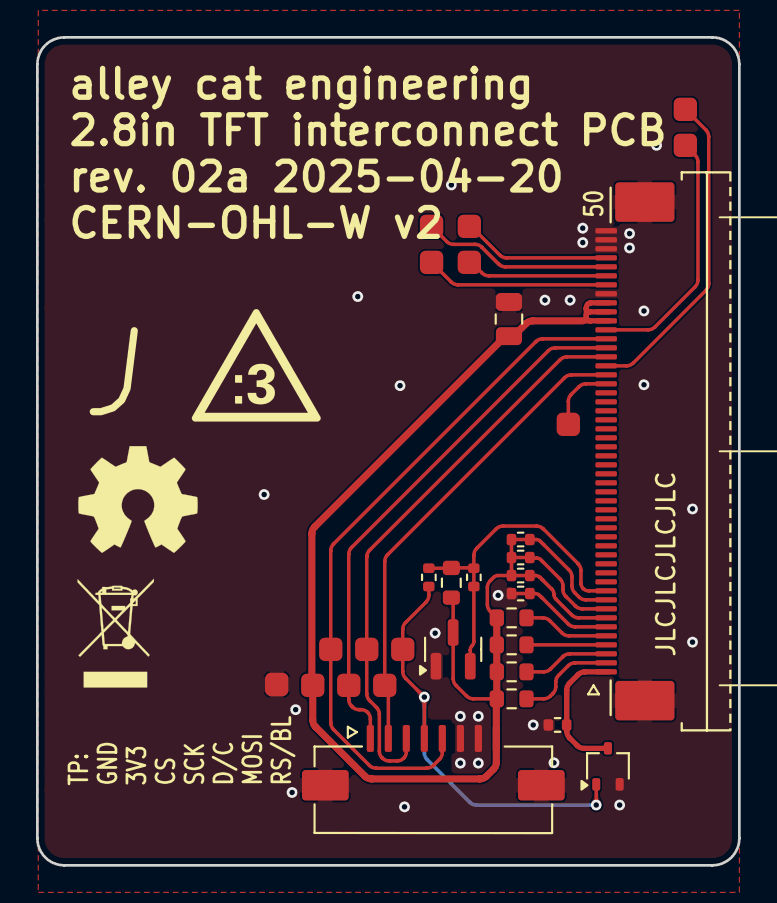
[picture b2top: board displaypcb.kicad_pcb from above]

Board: 2 copper layers, 39.0 x 46.0 mm, 32 parts (1 on the bottom side), 25 nets.

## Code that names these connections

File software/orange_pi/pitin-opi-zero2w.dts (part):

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// Needs the Armbian sunxi kernel: its AHUB audio and H616 PWM drivers are not in mainline.
//
// Header pin -> H618 pin (Orange Pi wiringOP table) -> use on the Pi Tin board:
//   5  PI7   power-off output (SHUTDOWN_PS)   16 PI14 backlight (RS/BL), PWM4
//   8  PH0   USB cable detect (USB_PWR)       19 PH7  SPI1 MOSI
//  12  PI1   I2S0 BCLK                        21 PH8  LED gate (LED_CS), SPI1 chip select 1 as GPIO
//  22  PI6   display D/C                      23 PH6  SPI1 CLK
//  24  PH5   SPI1 CS0 (display)               26 PH9  power button (SHUTDOWN_PI)
//  35  PI2   I2S0 LRCK                        40 PI3  I2S0 DOUT0 -> MAX98357A
//  Buttons: 7 LEFT PI13, 10 RIGHT PH1, 11 DOWN PH2, 13 L1 PH3, 15 L2 PI5, 18 UP PH4,
//  27 SPECIAL PI10, 28 R2 PI9, 29 SELECT PI0, 31 R1 PI15, 32 A PI11, 33 START PI12,
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

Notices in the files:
kicad/pcb_display_r2a/displaypcb.kicad_pcb:
Released under the CERN-OHL-W V2 license
